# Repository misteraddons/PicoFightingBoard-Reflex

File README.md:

# Reflex Fighting Board

Open source PCB for arcade sticks using Raspberry Pi Pico's RP2040 microcontroller.

## Introduction

They say imitation is the highest form of flattery. If that's the case then the Brook line of arcade controller boards must be blushing beet red. The Reflex Fighting Board uses the same form factor and layout of the Brook PCBs to maintain compatibility with existing arcade stick cases, wiring harnesses, wire management accessories, etc.

The files for PCB production are in the [Releases](https://github.com/misteraddons/ReflexFightingBoard/tree/main/boards/Reflex_V1) section. The zip file contains the Gerber and drill files, which is all you'll need if you're soldering SMT components yourself. There are also `csv` files for the BOM (Bill of Materials) and component positioning for SMT assembly service.

I will also have premade boards periodically available for purchase at <https://misteraddons.com/collections/parts/products/reflex-encode-fighting-board>.

## Versions, Errata & Changelog

Reflex Encode V1.0:

>RGB LED voltage too low - voltage source moved to Vbus (before fuse) instead of +5V (after fuse)

>Pinout = PicoFightingBoard

Reflex Encode V1.1:

>Added USB A connector

>Added 5 pin USB header

>Pinout = GP2040

>Added turbo button

>Added turbo LED

>Added spinner header

>Error: Left and Right pins swapped compared to GP2040 pinout

>Error: TP+L3+R3 pinout incompatible with Brook cable

Reflex Encode V1.2:

>Fixed Left / Right pinout

>Fixed TP+L3+R3 pinout

## Firmware

The [GP2040](https://github.com/OpenStickCommunity/GP2040-CE) gamepad firmware for Pi Pico/RP2040 has a pre-configured build for use with the Reflex Fighting Board, providing support for XInput (PC, Android, Raspberry Pi, etc.), DInput (PC/PS3) and Nintendo Switch. [Go to the releases](https://github.com/OpenStickCommunity/GP2040-CE/releases) and download the `GP2040-CE_X.X.X_PicoFightingBoard.uf2`. To flash:

1. Unplug your Reflex Fighting Board.
1. Hold the BOOTSEL button on the Pico and plug into your computer. A new removable drive named `RPI-RP2` should appear in your file explorer.
1. Drag and drop the `GP2040-CE_X.X.X_PicoFightingBoard.uf2` file into the removable drive. This will flash the board.
1. The board should now be running the GP2040 firmware and should appear as a controller on your computer.

## Modification

If you want to modify the PCB layout you'll need the free [KiCad software](https://www.kicad.org/download/) installed. KiCad 6.x/7.x was used for these instructions.

## Support

If you would like to discuss and issues or features with the Reflex Fighting Board, please join the [OpenStick GP2040-CE Discord server](https://discord.gg/k2pxhke7q8) or the [MiSTer Addons Discord server](https://discord.gg/PtUFHtzuYD).

## Contributions

Want to help improve the Reflex Fighting Board? There are a bunch of ways to contribute!

### Pull Requests

Pull requests are welcome and encouraged for enhancements, fixes and documentation updates.

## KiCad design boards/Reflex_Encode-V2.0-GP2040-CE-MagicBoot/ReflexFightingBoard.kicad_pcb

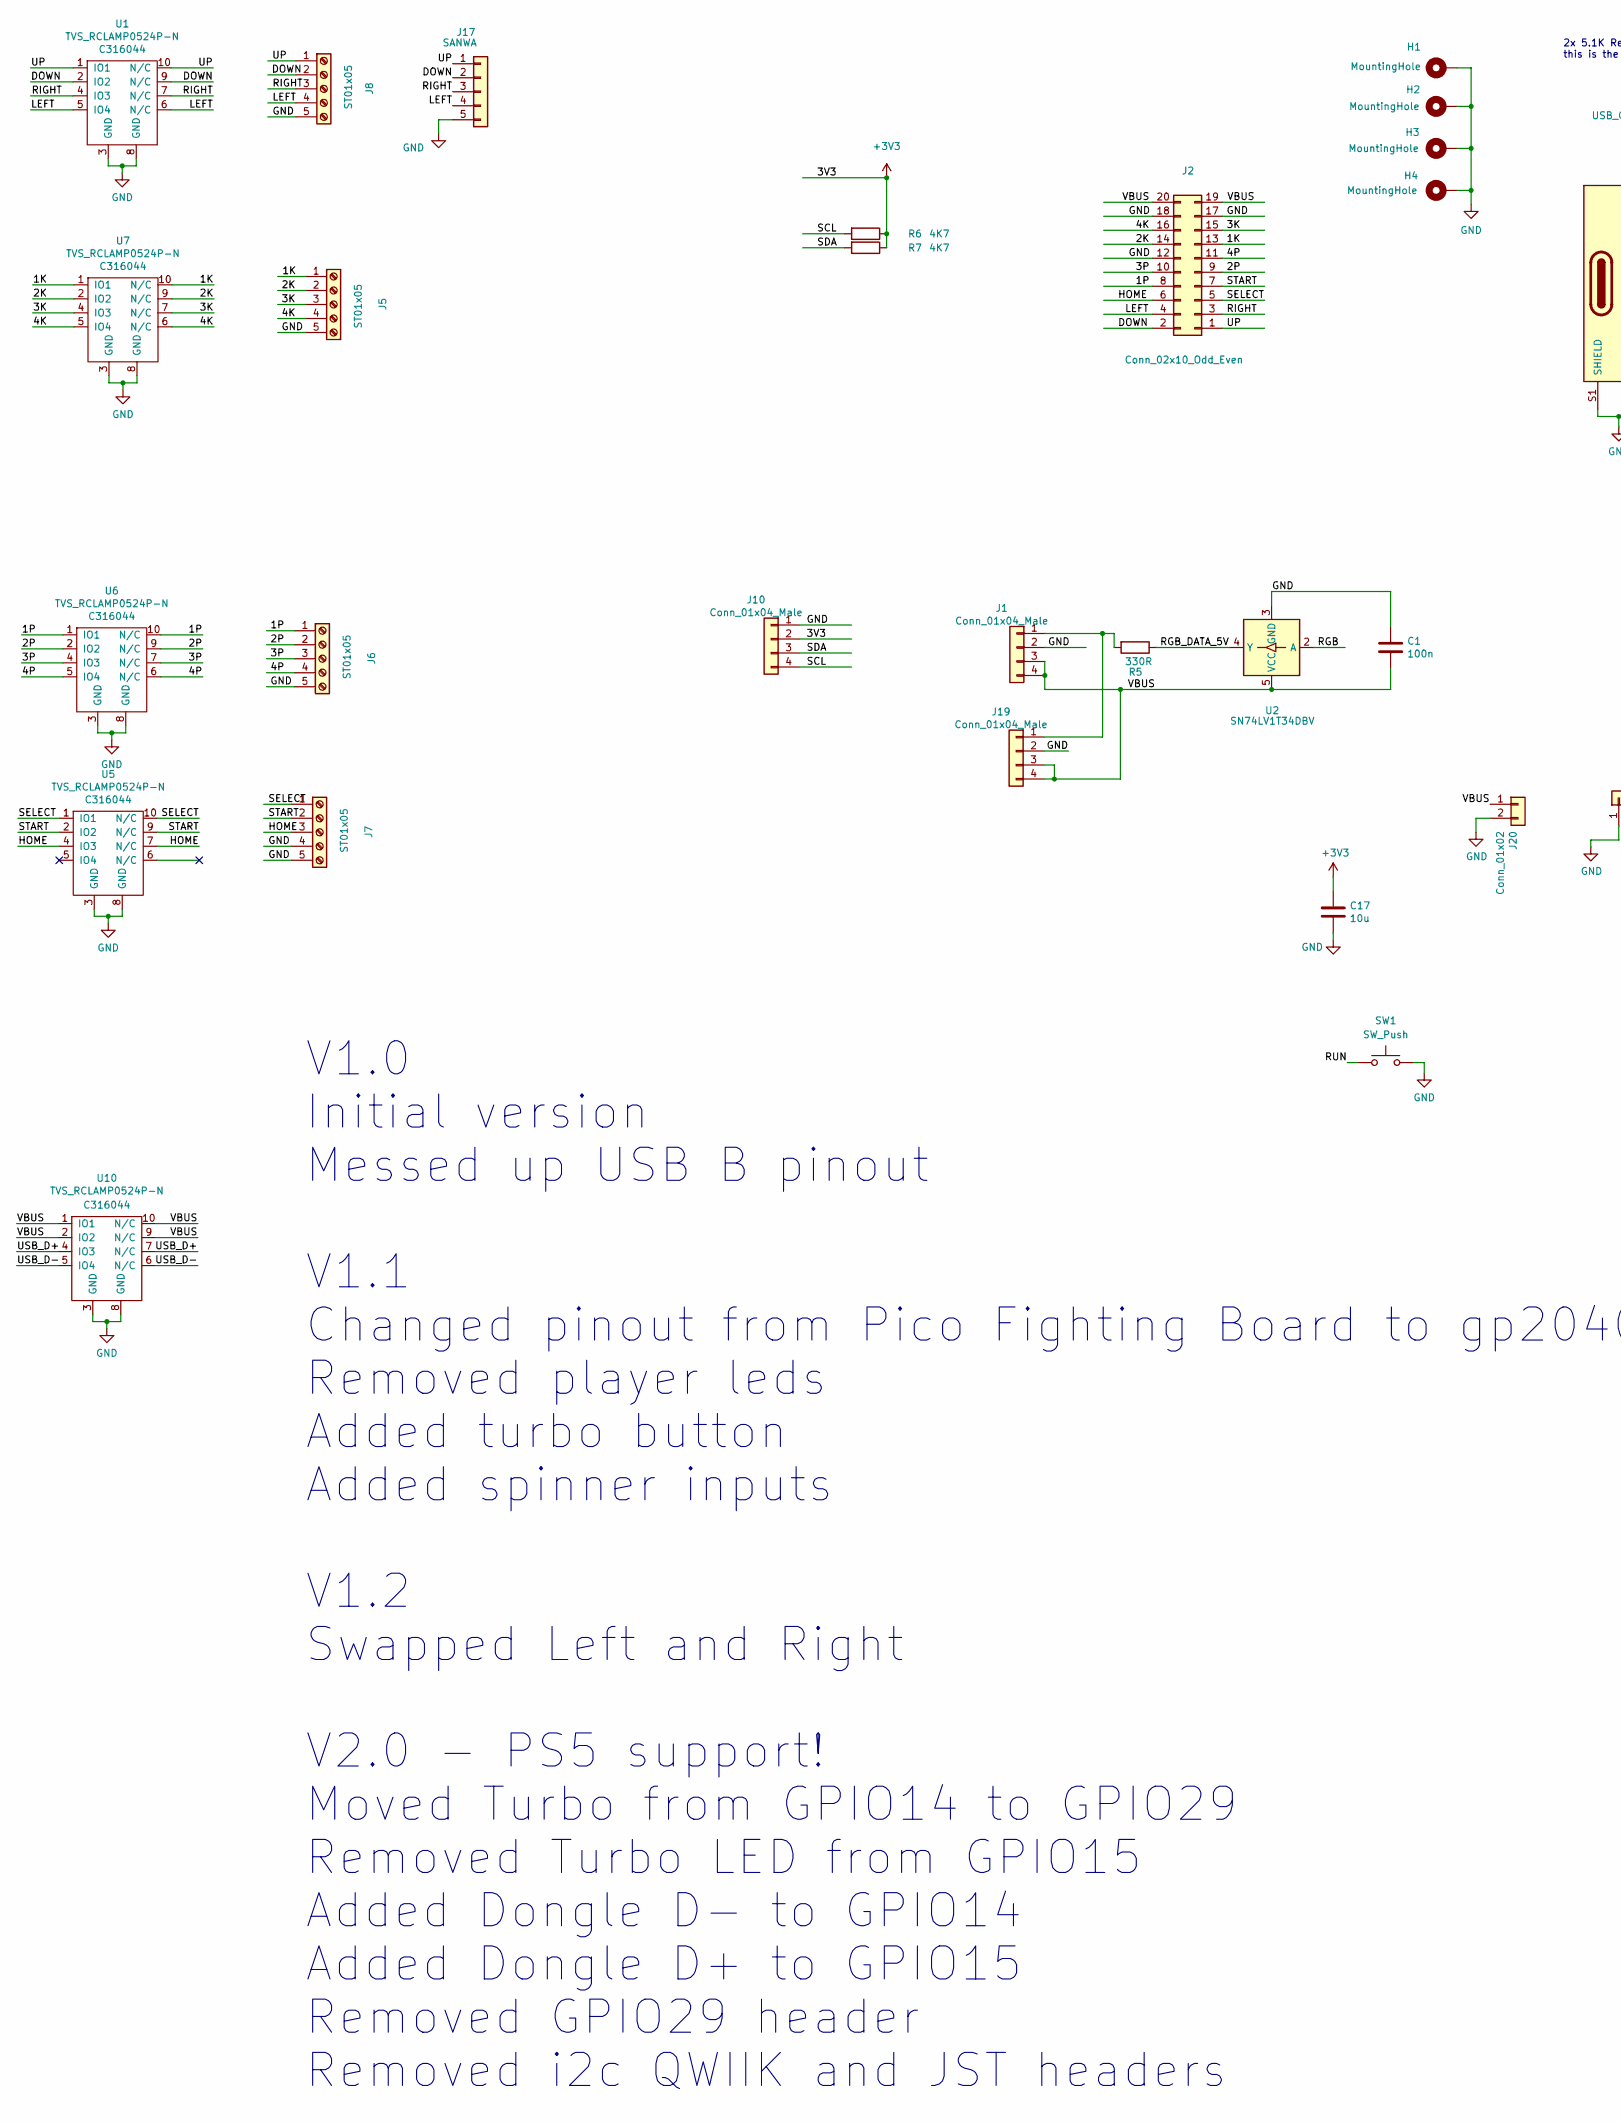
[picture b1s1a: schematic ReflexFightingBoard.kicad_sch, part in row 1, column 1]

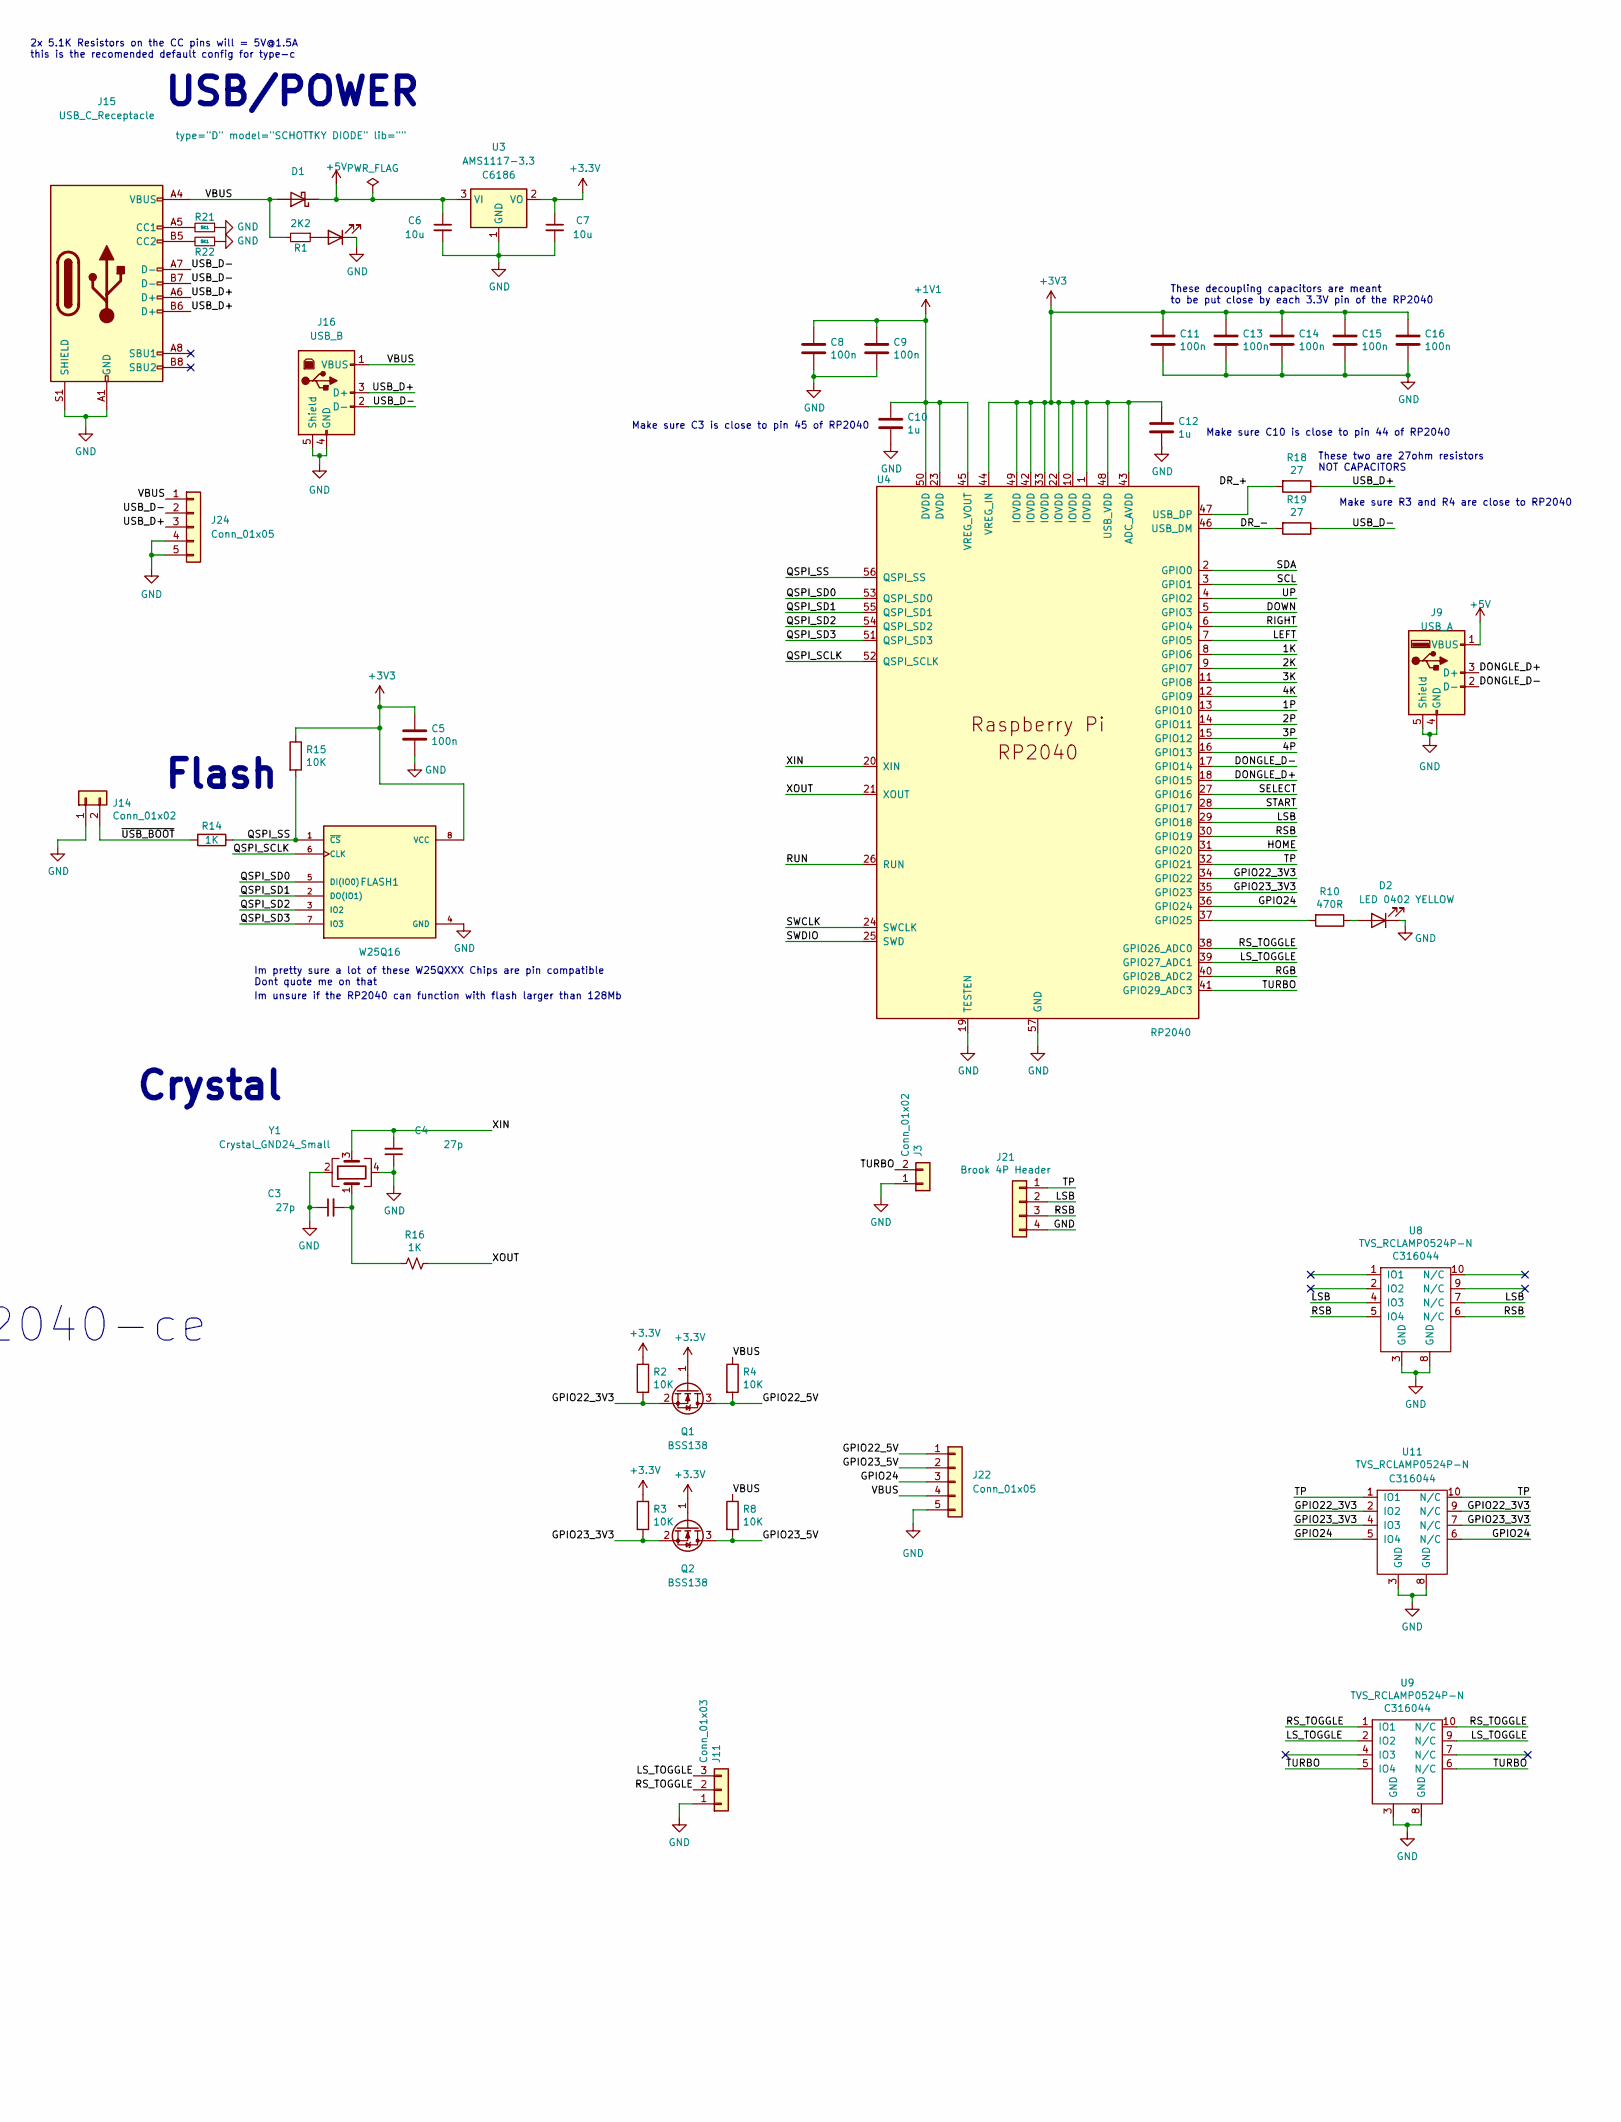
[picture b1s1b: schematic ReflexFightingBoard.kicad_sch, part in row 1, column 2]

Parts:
C1, C5, C8, C9, C11, C13, C14, C15, C16: 100n; C_0402_1005Metric; LCSC Part C1525
C3, C4: 27p; C_0402_1005Metric; LCSC Part C1557
C6, C7, C17: 10u; C_0402_1005Metric; LCSC Part C15525
C10, C12: 1u; C_0402_1005Metric; LCSC Part C52923
D1: type="D" model="SCHOTTKY DIODE" lib=""; D_0603_1608Metric; LCSC Part C143772
D2: LED; LED_0603_1608Metric; LCSC Part C5137313
FLASH1: W25Q16; SOIC127P790X216-8N; LCSC Part C82317
H1, H2, H3, H4: MountingHole; MountingHole_3.5mm_Pad
J1: Conn_01x04_Male; JST_PH_B4B-PH-K_1x04_P2.00mm_Vertical; LCSC Part C131334
J2: Conn_02x10_Odd_Even; PinHeader_2x10_P2.54mm_Vertical; LCSC Part C492427
J3: Conn_01x02; JST_PH_B2B-PH-K_1x02_P2.00mm_Vertical; LCSC Part C722767
J5, J6, J7, J8: ST01x05; TerminalBlock_MetzConnect_Type059_RT06305HBWC_1x05_P3.50mm_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; LCSC Part C3646874
J9: USB_A; USB2_A_HOR_C42425; LCSC Part C42425
J10, J19: Conn_01x04_Male; PinHeader_1x04_P2.54mm_Vertical; LCSC Part C2935910
J11: Conn_01x03; JST_PH_B3B-PH-K_1x03_P2.00mm_Vertical; LCSC Part C722771
J14, J20: Conn_01x02; PinHeader_1x02_P2.54mm_Vertical; LCSC Part C492401
J15: USB_C_Receptacle; USB_Type_C_C167321; LCSC Part C165948
J16: USB_B; USB_B_Lumberg_2411_02_Horizontal; LCSC Part C388656
J17: SANWA; JST_XH_B5B-XH-AM_1x05_P2.50mm_Vertical; LCSC Part C2908603
J21: Brook 4P Header; JST_PH_B4B-PH-K_1x04_P2.00mm_Vertical; LCSC Part C722775
J22, J24: Conn_01x05; PinHeader_1x05_P2.54mm_Vertical; LCSC Part C124379
Q1, Q2: BSS138; SOT-23; LCSC Part C8545
R1: 2K2; R_0402_1005Metric; LCSC Part C25879
R2, R3, R4, R8, R15: 10K; R_0402_1005Metric; LCSC Part C25744
R5: 330R; R_0402_1005Metric; LCSC Part C25104
R6, R7: 4K7; R_0402_1005Metric; LCSC Part C25900
R10: 470R; R_0402_1005Metric; LCSC Part C25117
R14: 1K; C_0402_1005Metric; LCSC Part C11702
R16: 1K; R_0402_1005Metric; LCSC Part C11702
R18, R19: 27; R_0402_1005Metric; LCSC Part C25100
R21, R22: 5K1; R_0402_1005Metric; LCSC Part C25905
SW1: SW_Push; SW_SPST_6x6_C499305_C499302; LCSC Part C499305
U1, U5, U6, U7, U8, U9, U10, U11: TVS_RCLAMP0524P-N; UDFN-10_1.35x2.6mm_P0.5mm; LCSC Part C316044
U2: SN74LV1T34DBV; SOT-23-5; LCSC Part C100024
U3: AMS1117-3.3; SOT-223-3_TabPin2; LCSC Part C6186
U4: RP2040; RP2040-QFN-56; LCSC Part C2040
Y1: Crystal_GND24_Small; Crystal_SMD_SeikoEpson_TSX3225-4Pin_3.2x2.5mm; LCSC Part C9002

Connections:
+1V1: C8.1, C9.1, C10.1, U4.23 (DVDD), U4.45 (VREG_VOUT), U4.50 (DVDD)
+5V: C6.1, D1.1 (K), J9.1 (VBUS), U3.3 (VI)
/1K: J2.13, J5.1, U4.8 (GPIO6), U7.1 (IO1), U7.10 (N/C)
/1P: J2.8, J6.1, U4.13 (GPIO10), U6.1 (IO1), U6.10 (N/C)
/2K: J2.14, J5.2, U4.9 (GPIO7), U7.2 (IO2), U7.9 (N/C)
/2P: J2.9, J6.2, U4.14 (GPIO11), U6.2 (IO2), U6.9 (N/C)
/3K: J2.15, J5.3, U4.11 (GPIO8), U7.4 (IO3), U7.7 (N/C)
/3P: J2.10, J6.3, U4.15 (GPIO12), U6.4 (IO3), U6.7 (N/C)
/4K: J2.16, J5.4, U4.12 (GPIO9), U7.5 (IO4), U7.6 (N/C)
/4P: J2.11, J6.4, U4.16 (GPIO13), U6.5 (IO4), U6.6 (N/C)
/DONGLE_D+: J9.3 (D+), U4.18 (GPIO15)
/DONGLE_D-: J9.2 (D-), U4.17 (GPIO14)
/DOWN: J2.2, J8.2, J17.2, U1.2 (IO2), U1.9 (N/C), U4.5 (GPIO3)
/DR_+: R18.2, U4.47 (USB_DP)
/DR_-: R19.2, U4.46 (USB_DM)
/GPIO22_3V3: Q1.2 (S), R2.2, U4.34 (GPIO22), U11.2 (IO2), U11.9 (N/C)
/GPIO22_5V: J22.1, Q1.3 (D), R4.2
/GPIO23_3V3: Q2.2 (S), R3.2, U4.35 (GPIO23), U11.4 (IO3), U11.7 (N/C)
/GPIO23_5V: J22.2, Q2.3 (D), R8.2
/GPIO24: J22.3, U4.36 (GPIO24), U11.5 (IO4), U11.6 (N/C)
/HOME: J2.6, J7.3, U4.31 (GPIO20), U5.4 (IO3), U5.7 (N/C)
/LEFT: J2.4, J8.4, J17.4, U1.5 (IO4), U1.6 (N/C), U4.7 (GPIO5)
/LSB: J21.2, U4.29 (GPIO18), U8.4 (IO3), U8.7 (N/C)
/LS_TOGGLE: J11.3, U4.39 (GPIO27_ADC1), U9.2 (IO2), U9.9 (N/C)
/QSPI_SCLK: FLASH1.6 (CLK), U4.52 (QSPI_SCLK)
/QSPI_SD0: FLASH1.5 (DI(IO0)), U4.53 (QSPI_SD0)
/QSPI_SD1: FLASH1.2 (DO(IO1)), U4.55 (QSPI_SD1)
/QSPI_SD2: FLASH1.3 (IO2), U4.54 (QSPI_SD2)
/QSPI_SD3: FLASH1.7 (IO3), U4.51 (QSPI_SD3)
/QSPI_SS: FLASH1.1 (~CS), R14.1, R15.2, U4.56 (QSPI_SS)
/RGB: U2.2 (A), U4.40 (GPIO28_ADC2)
/RGB_DATA_5V: R5.1, U2.4 (Y)
/RIGHT: J2.3, J8.3, J17.3, U1.4 (IO3), U1.7 (N/C), U4.6 (GPIO4)
/RSB: J21.3, U4.30 (GPIO19), U8.5 (IO4), U8.6 (N/C)
/RS_TOGGLE: J11.2, U4.38 (GPIO26_ADC0), U9.1 (IO1), U9.10 (N/C)
/RUN: SW1.1, U4.26 (RUN)
/SCL: J10.4, R6.2, U4.3 (GPIO1)
/SDA: J10.3, R7.2, U4.2 (GPIO0)
/SELECT: J2.5, J7.1, U4.27 (GPIO16), U5.1 (IO1), U5.10 (N/C)
/START: J2.7, J7.2, U4.28 (GPIO17), U5.2 (IO2), U5.9 (N/C)
/SWCLK: U4.24 (SWCLK)
/SWDIO: U4.25 (SWD)
/TP: J21.1, U4.32 (GPIO21), U11.1 (IO1), U11.10 (N/C)
/TURBO: J3.2, U4.41 (GPIO29_ADC3), U9.5 (IO4), U9.6 (N/C)
/UP: J2.1, J8.1, J17.1, U1.1 (IO1), U1.10 (N/C), U4.4 (GPIO2)
/USB_D+: J15.A6 (D+), J15.B6 (D+), J16.3 (D+), J24.3, R18.1, U10.4 (IO3), U10.7 (N/C)
/USB_D-: J15.A7 (D-), J15.B7 (D-), J16.2 (D-), J24.2, R19.1, U10.5 (IO4), U10.6 (N/C)
/VBUS: C1.2, D1.2 (A), J1.3, J1.4, J2.19, J2.20, J15.A4 (VBUS), J15.A9 (VBUS), J15.B4 (VBUS), J15.B9 (VBUS), J16.1 (VBUS), J19.3, J19.4, J20.1, J22.4, J24.1, R4.1, R8.1, U2.5 (VCC), U10.1 (IO1), U10.2 (IO2), U10.9 (N/C), U10.10 (N/C); also elsewhere on the board
/XIN: C4.2, U4.20 (XIN), Y1.3
/XOUT: R16.1, U4.21 (XOUT)
/~USB_BOOT: J14.2, R14.2
GND: C1.1, C3.1, C4.1, C5.2, C6.2, C7.2, C8.2, C9.2, C10.2, C11.2, C12.2, C13.2, C14.2, C15.2, C16.2, C17.2, D2.1 (K), FLASH1.4 (GND), H1.1, H2.1, H3.1, H4.1, J1.2, J2.12, J2.17, J2.18, J3.1, J5.5, J6.5, J7.4, J7.5, J8.5, J9.4 (GND), J9.5 (Shield), J10.1, J11.1, J14.1, J15.A1 (GND), J15.A12 (GND), J15.B1 (GND), J15.B12 (GND), J15.S1 (SHIELD), J16.4 (GND), J16.5 (Shield), J17.5, J19.2, J20.2, J21.4, J22.5, J24.4, J24.5, R21.1, R22.1, SW1.2, U1.3 (GND), U1.8 (GND), U2.3 (GND), U3.1 (GND), U4.19 (TESTEN), U4.57 (GND), U5.3 (GND), U5.8 (GND), U6.3 (GND), U6.8 (GND), U7.3 (GND), U7.8 (GND), U8.3 (GND), U8.8 (GND), U9.3 (GND), U9.8 (GND), U10.3 (GND), U10.8 (GND), U11.3 (GND), U11.8 (GND), Y1.2, Y1.4; also elsewhere on the board
unnamed: C3.2, R16.2, Y1.1
unnamed: J1.1, J19.1, R5.2
unnamed: J15.A5 (CC1), R21.2
unnamed: J15.B5 (CC2), R22.2
unnamed: R10.2, U4.37 (GPIO25)

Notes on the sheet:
Im pretty sure a lot of these W25QXXX Chips are pin compatible Dont quote me on that
Make sure C3 is close to pin 45 of RP2040
Make sure R3 and R4 are close to RP2040
These decoupling capacitors are meant to be put close by each 3.3V pin of the RP2040
These two are 27ohm resistors NOT CAPACITORS
Make sure C10 is close to pin 44 of RP2040
Flash
V1.0 Initial version Messed up USB B pinout V1.1 Changed pinout from Pico Fighting Board to gp2040-ce Removed player leds Added turbo button Added spinner inputs V1.2 Swapped Left and Right V2.0 - PS5 support! Moved Turbo from GPIO14 to GPIO29 Removed Turbo LED from GPIO15 Added Dongle D- to GPIO14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
2x 5.1K Resistors on the CC pins will = 5V@1.5A this is the recomended default config for type-c
Im unsure if the RP2040 can function with flash larger than 128Mb
USB/POWER
Crystal

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
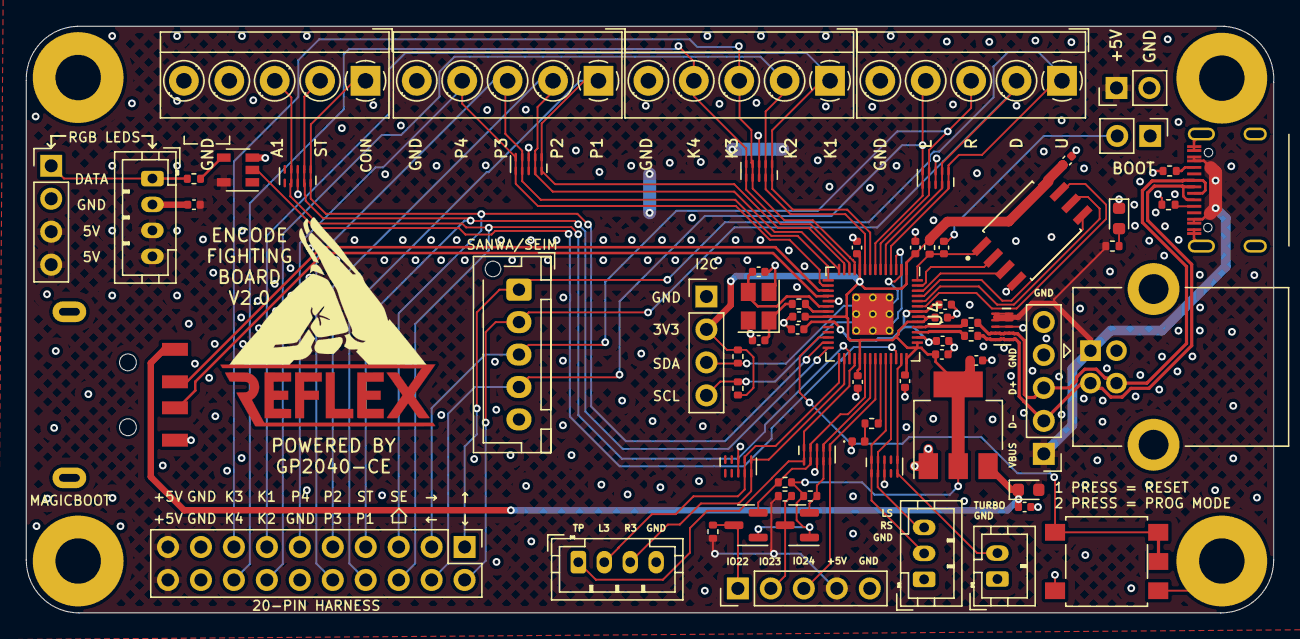
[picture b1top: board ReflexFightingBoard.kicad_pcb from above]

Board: 4 copper layers, 96.1 x 45.2 mm, 77 parts (1 on the bottom side), 58 nets.

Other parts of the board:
D3: LED; LED_0603_1608Metric
R9: 2K2; R_0402_1005Metric
Ref**: Val**; Reflex_Copper_20mm
Ref**#2: Val**; Reflex_Encode-Kung_Fu-Silk-15mm
Ref**#3: Val**; Idaho_M

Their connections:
/VBUS: R9.2; also elsewhere on the board
GND: D3.1 (K); also elsewhere on the board

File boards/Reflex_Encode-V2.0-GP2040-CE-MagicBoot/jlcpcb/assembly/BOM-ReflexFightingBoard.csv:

Comment,Designator,Footprint,LCSC
SN74LV1T34DBV,U2,SOT-23-5,C100024
1K,"R1,R14,R16",R_0402_1005Metric,C11702
Conn_01x05,"J22,J24",PinHeader_1x05_P2.54mm_Vertical,C124379
LED 0402 YELLOW,D2,LED_0402_1005Metric,C130719
Conn_01x04_Male,"J1,J12",JST_PH_B4B-PH-K_1x04_P2.00mm_Vertical,C131334
SCHOTTKY DIODE,D1,D_0603_1608Metric,C143772
Conn_01x04_Male,"J13,J9",BOOM_SH_C145961_1x04_P1.00mm_Vertical,C145961
100n,"C1,C11,C13,C14,C15,C16,C5,C8,C9",C_0402_1005Metric,C1525
10u,"C17,C6,C7",C_0402_1005Metric,C15525
27p,"C3,C4",C_0402_1005Metric,C1557
USB_C_Receptacle,J15,USB_Type_C_C167321,C165948
RP2040,U4,RP2040-QFN-56,C2040
27,"R18,R19",R_0402_1005Metric,C25100
330R,R5,R_0402_1005Metric,C25104
470R,R20,R_0402_1005Metric,C25117
10K,"R15,R2,R3,R4,R8",R_0402_1005Metric,C25744
4K7,"R6,R7",R_0402_1005Metric,C25900
5K1,"R21,R22",R_0402_1005Metric,C25905
SANWA,"J17,J18",JST_XH_B5B-XH-AM_1x05_P2.50mm_Vertical,C2908603
Conn_01x03,J11,JST_PH_B3B-PH-K_1x03_P2.00mm_Vertical,C2908624
Conn_01x04_Male,"J10,J19",PinHeader_1x04_P2.54mm_Vertical,C2935910
TVS_RCLAMP0524P-N,"U1,U10,U11,U5,U6,U7,U8,U9",UDFN-10_1.35x2.6mm_P0.5mm,C316044
ST01x05,"J5,J6,J7,J8",TerminalBlock_MetzConnect_Type059_RT06305HBWC_1x05_P3.50mm_Horizontal,C3646874
USB_B,J16,USB_B_Lumberg_2411_02_Horizontal,C388656
Conn_01x02,J20,PinHeader_1x02_P2.54mm_Vertical,C492401
Conn_02x10_Odd_Even,J2,PinHeader_2x10_P2.54mm_Vertical,C492427
SW_Push,SW1,SW_SPST_6x6_C499305_C499302,C499305
1u,"C10,C12",C_0402_1005Metric,C52923
AMS1117-3.3,U3,SOT-223-3_TabPin2,C6186
Conn_01x02,"J26,J3,J4",JST_PH_B2B-PH-K_1x02_P2.00mm_Vertical,C722767
Brook 4P Header,J21,JST_PH_B4B-PH-K_1x04_P2.00mm_Vertical,C722775
W25Q16,FLASH1,SOIC127P790X216-8N,C82317
BSS138,"Q1,Q2",SOT-23,C8545
Crystal_GND24_Small,Y1,Crystal_SMD_SeikoEpson_TSX3225-4Pin_3.2x2.5mm,C9002
Conn_01x02,J14,PinHeader_1x02_P2.54mm_Vertical,

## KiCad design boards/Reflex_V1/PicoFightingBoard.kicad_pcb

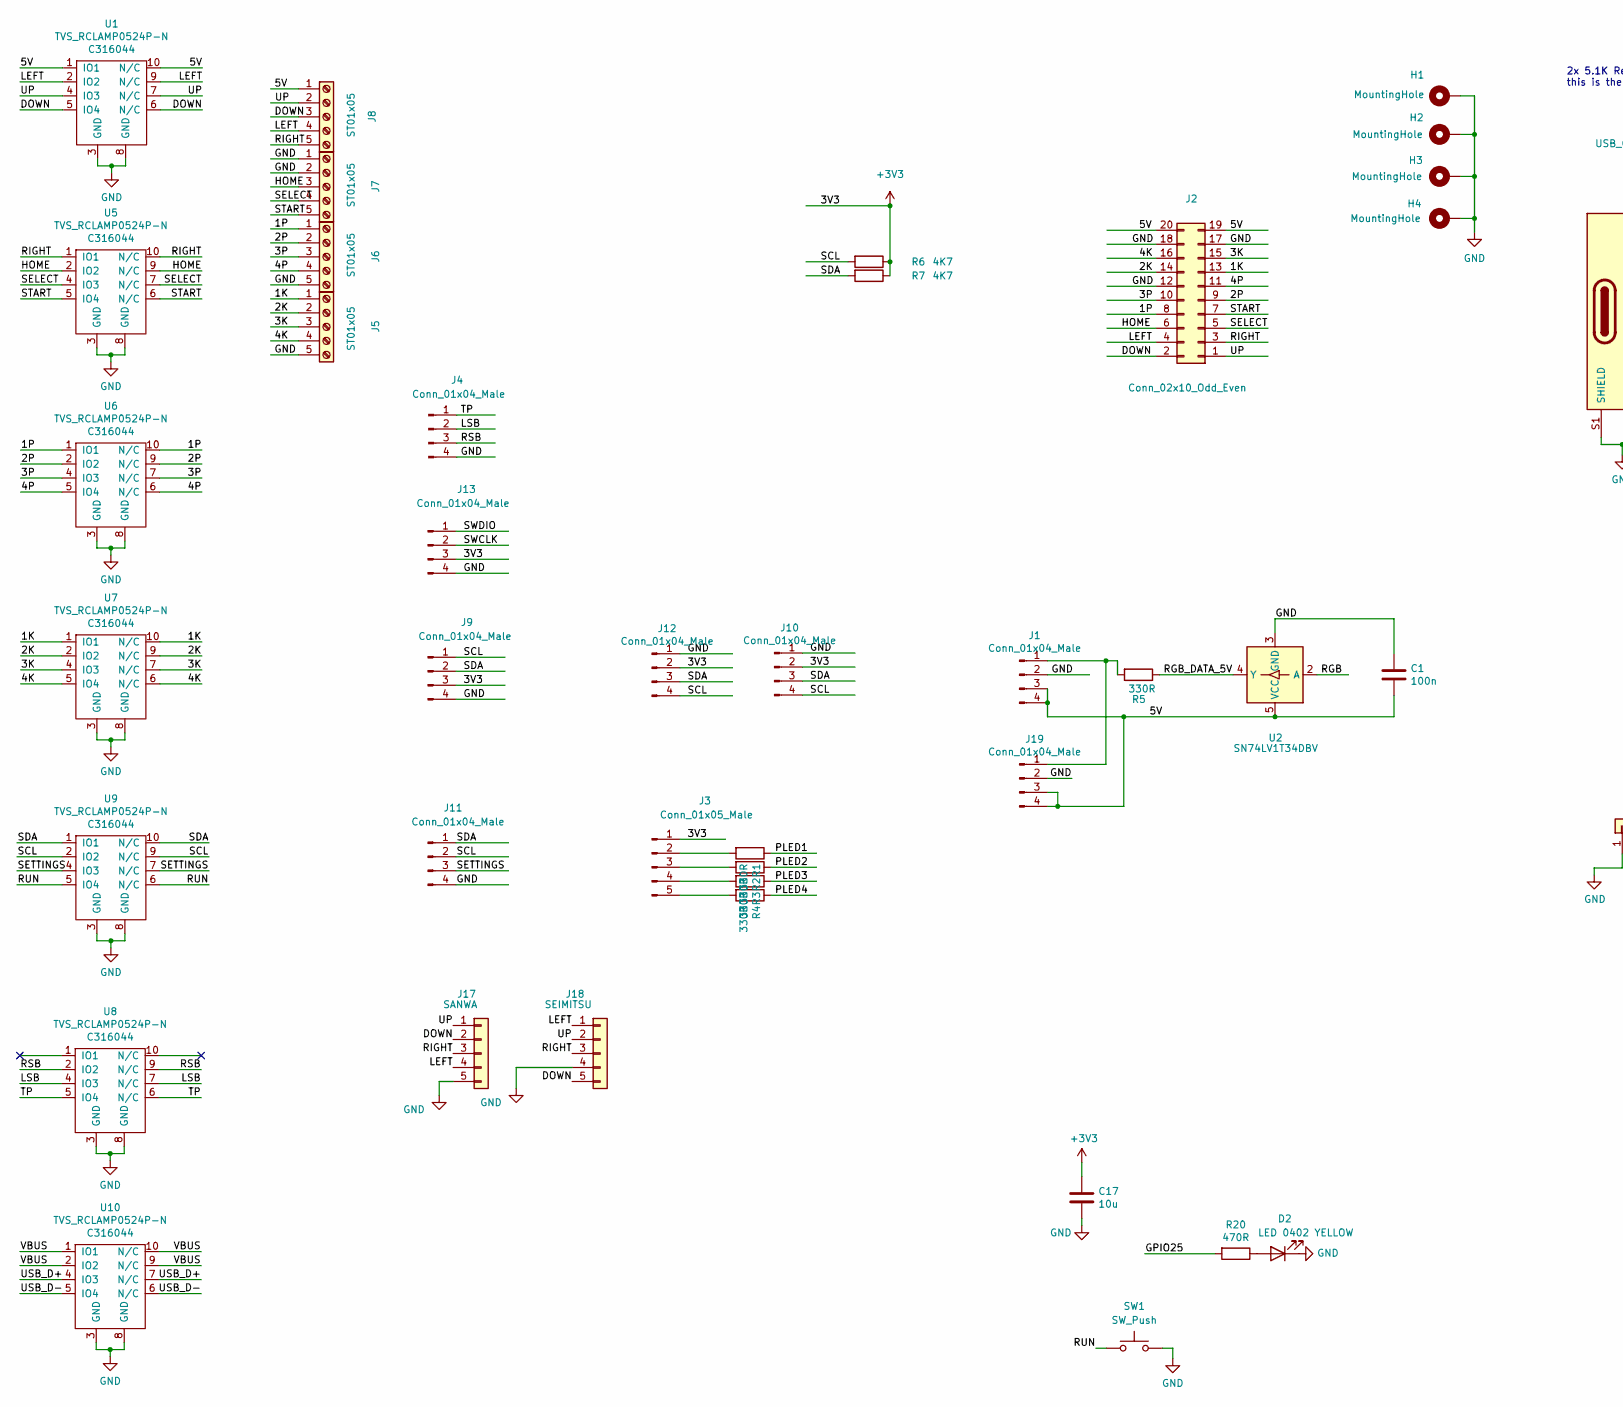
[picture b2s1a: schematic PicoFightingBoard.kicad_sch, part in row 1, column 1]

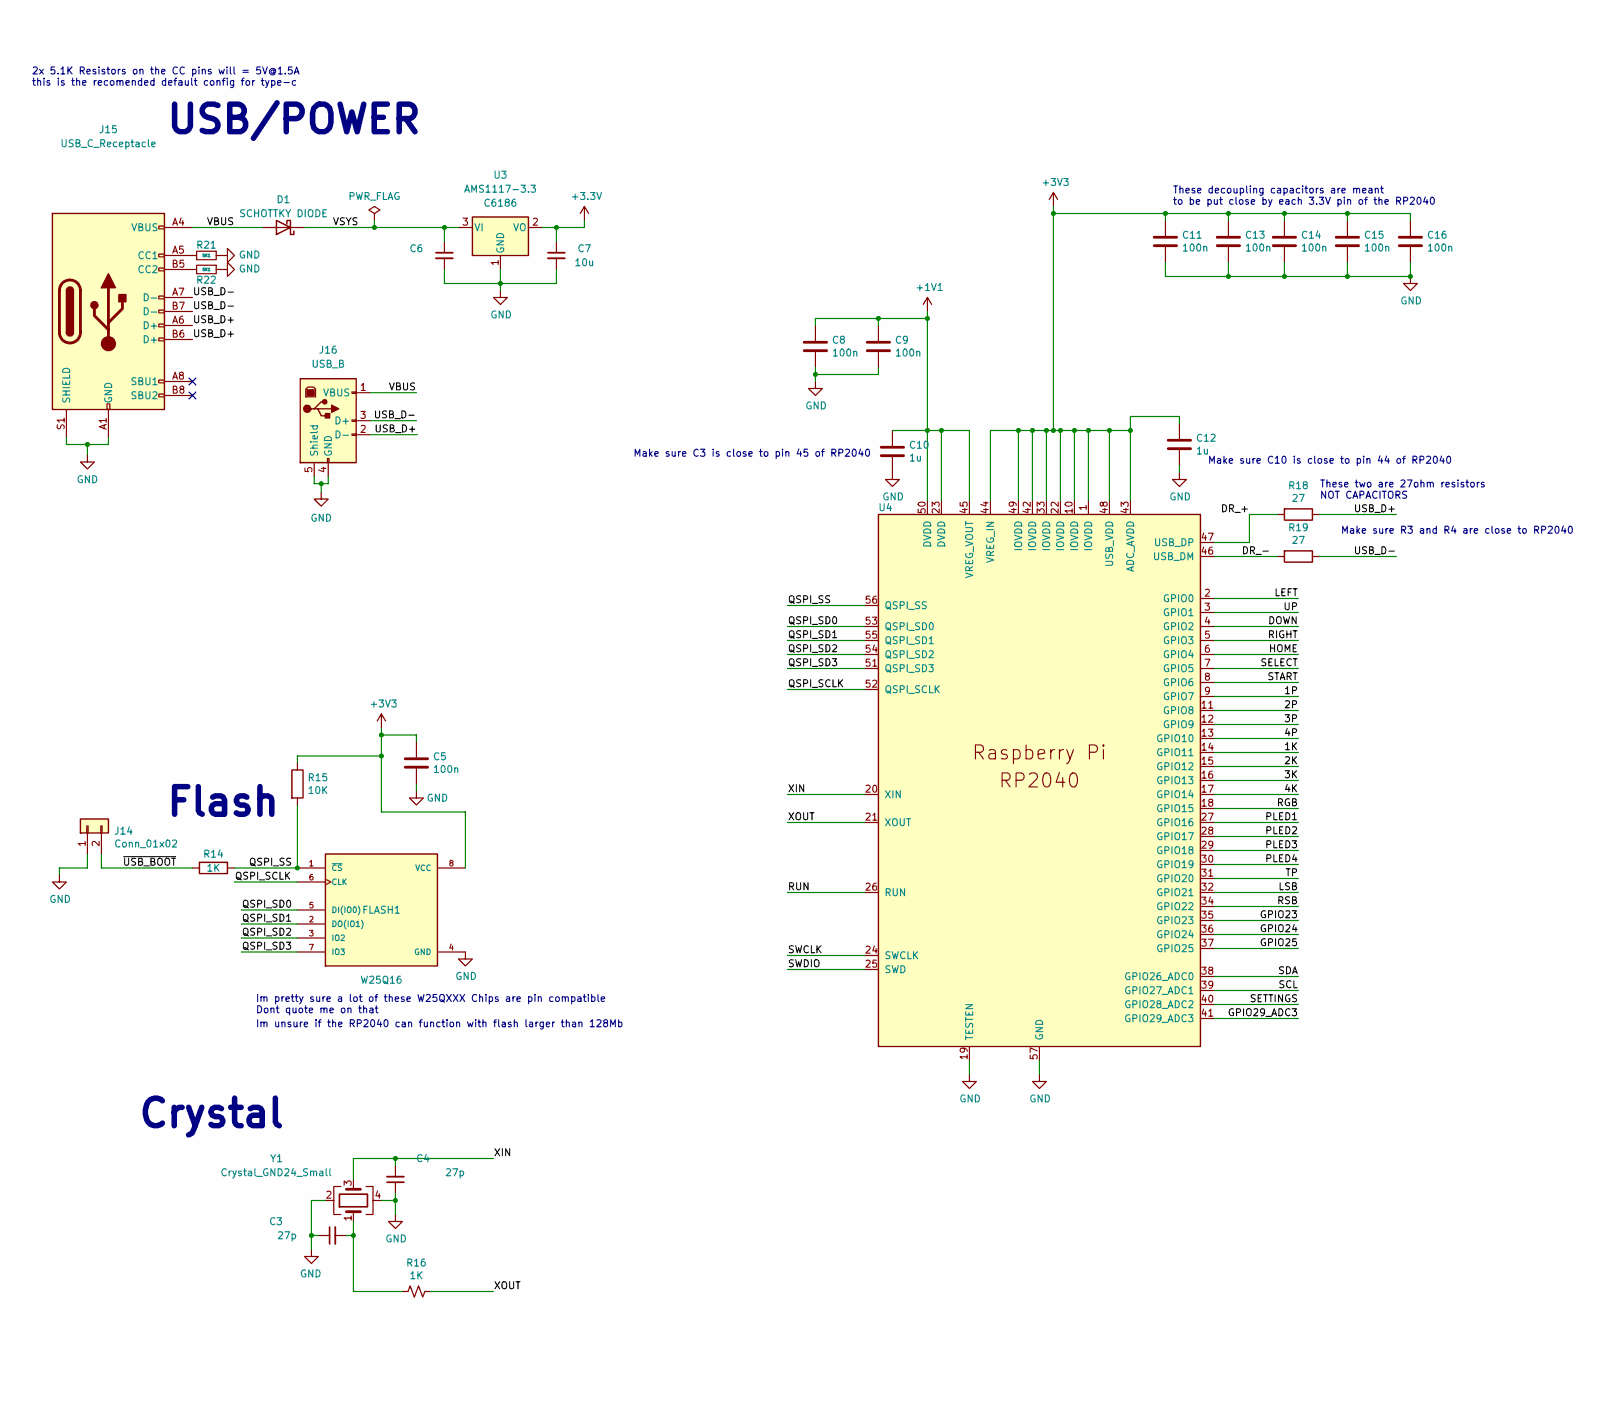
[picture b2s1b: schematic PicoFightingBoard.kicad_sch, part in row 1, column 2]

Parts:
C1, C5, C8, C9, C11, C13, C14, C15, C16: 100n; C_0402_1005Metric; LCSC Part C1525
C3, C4: 27p; C_0402_1005Metric; LCSC Part C1557
C6: LCSC Part C15525
C7, C17: 10u; C_0402_1005Metric; LCSC Part C15525
C10, C12: 1u; C_0402_1005Metric; LCSC Part C52923
D1: SCHOTTKY DIODE; D_0603_1608Metric; LCSC Part C143772
D2: LED 0402 YELLOW; LED_0402_1005Metric; LCSC Part C130719
FLASH1: W25Q16; SOIC127P790X216-8N; LCSC Part C82317
H1, H2, H3, H4: MountingHole; MountingHole_3.5mm_Pad
J1, J4, J11, J12: Conn_01x04_Male; JST_PH_B4B-PH-K_1x04_P2.00mm_Vertical; LCSC Part C131334
J2: Conn_02x10_Odd_Even; PinHeader_2x10_P2.54mm_Vertical; LCSC Part C492427
J3: Conn_01x05_Male; JST_PH_B5B-PH-K_1x05_P2.00mm_Vertical
J5, J6, J7, J8: ST01x05; TerminalBlock_MetzConnect_Type059_RT06305HBWC_1x05_P3.50mm_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; LCSC Part C3646874
J9, J13: Conn_01x04_Male; BOOM_SH_C145961_1x04_P1.00mm_Vertical; LCSC Part C145961
J10, J19: Conn_01x04_Male; PinHeader_1x04_P2.54mm_Vertical; LCSC Part C2935910
J14: Conn_01x02; PinHeader_1x02_P2.54mm_Vertical
J15: USB_C_Receptacle; USB_Type_C_C167321; LCSC Part C167321
J16: USB_B; USB_B_Lumberg_2411_02_Horizontal; LCSC Part C388656
J17: SANWA; JST_XH_B5B-XH-AM_1x05_P2.50mm_Vertical; LCSC Part C2908603
J18: SEIMITSU; JST_XH_B5B-XH-AM_1x05_P2.50mm_Vertical; LCSC Part C2908603
R1, R2, R3, R4, R5: 330R; R_0402_1005Metric; LCSC Part C25104
R6, R7: 4K7; R_0402_1005Metric; LCSC Part C25900
R14: 1K; C_0402_1005Metric; LCSC Part C11702
R15: 10K; R_0402_1005Metric; LCSC Part C25744
R16: 1K; R_0402_1005Metric; LCSC Part C11702
R18, R19: 27; R_0402_1005Metric; LCSC Part C25100
R20: 470R; R_0402_1005Metric; LCSC Part C25117
R21, R22: 5K1; R_0402_1005Metric; LCSC Part C25905
SW1: SW_Push; SW_SPST_6x6_C499305_C499302; LCSC Part C499305
U1, U5, U6, U7, U8, U9, U10: TVS_RCLAMP0524P-N; UDFN-10_1.35x2.6mm_P0.5mm; LCSC Part C316044
U2: SN74LV1T34DBV; SOT-23-5; LCSC Part C100024
U3: AMS1117-3.3; SOT-223-3_TabPin2; LCSC Part C6186
U4: LCSC Part C2040
Y1: Crystal_GND24_Small; Crystal_SMD_SeikoEpson_TSX3225-4Pin_3.2x2.5mm; LCSC Part C9002

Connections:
+1V1: C8.1, C9.1, C10.1, U4.23 (DVDD), U4.45 (VREG_VOUT), U4.50 (DVDD)
/1K: J2.13, J5.1, U4.14 (GPIO11), U7.1 (IO1), U7.10 (N/C)
/1P: J2.8, J6.1, U4.9 (GPIO7), U6.1 (IO1), U6.10 (N/C)
/2K: J2.14, J5.2, U4.15 (GPIO12), U7.2 (IO2), U7.9 (N/C)
/2P: J2.9, J6.2, U4.11 (GPIO8), U6.2 (IO2), U6.9 (N/C)
/3K: J2.15, J5.3, U4.16 (GPIO13), U7.4 (IO3), U7.7 (N/C)
/3P: J2.10, J6.3, U4.12 (GPIO9), U6.4 (IO3), U6.7 (N/C)
/4K: J2.16, J5.4, U4.17 (GPIO14), U7.5 (IO4), U7.6 (N/C)
/4P: J2.11, J6.4, U4.13 (GPIO10), U6.5 (IO4), U6.6 (N/C)
/5V: C1.2, J1.3, J1.4, J2.19, J2.20, J8.1, J19.3, J19.4, U1.1 (IO1), U1.10 (N/C), U2.5 (VCC)
/DOWN: J2.2, J8.3, J17.2, J18.5, U1.5 (IO4), U1.6 (N/C), U4.4 (GPIO2)
/DR_+: R18.2, U4.47 (USB_DP)
/DR_-: R19.2, U4.46 (USB_DM)
/GPIO23: U4.35 (GPIO23)
/GPIO24: U4.36 (GPIO24)
/GPIO25: R20.2, U4.37 (GPIO25)
/GPIO29_ADC3: U4.41 (GPIO29_ADC3)
/HOME: J2.6, J7.3, U4.6 (GPIO4), U5.2 (IO2), U5.9 (N/C)
/LEFT: J2.4, J8.4, J17.4, J18.1, U1.2 (IO2), U1.9 (N/C), U4.2 (GPIO0)
/LSB: J4.2, U4.32 (GPIO21), U8.4 (IO3), U8.7 (N/C)
/PLED1: R1.1, U4.27 (GPIO16)
/PLED2: R2.1, U4.28 (GPIO17)
/PLED3: R3.1, U4.29 (GPIO18)
/PLED4: R4.1, U4.30 (GPIO19)
/QSPI_SCLK: FLASH1.6 (CLK), U4.52 (QSPI_SCLK)
/QSPI_SD0: FLASH1.5 (DI(IO0)), U4.53 (QSPI_SD0)
/QSPI_SD1: FLASH1.2 (DO(IO1)), U4.55 (QSPI_SD1)
/QSPI_SD2: FLASH1.3 (IO2), U4.54 (QSPI_SD2)
/QSPI_SD3: FLASH1.7 (IO3), U4.51 (QSPI_SD3)
/QSPI_SS: FLASH1.1 (~CS), R14.1, R15.2, U4.56 (QSPI_SS)
/RGB: U2.2 (A), U4.18 (GPIO15)
/RGB_DATA_5V: R5.1, U2.4 (Y)
/RIGHT: J2.3, J8.5, J17.3, J18.3, U4.5 (GPIO3), U5.1 (IO1), U5.10 (N/C)
/RSB: J4.3, U4.34 (GPIO22), U8.2 (IO2), U8.9 (N/C)
/RUN: SW1.1, U4.26 (RUN), U9.5 (IO4), U9.6 (N/C)
/SCL: J9.1, J10.4, J11.2, J12.4, R6.2, U4.39 (GPIO27_ADC1), U9.2 (IO2), U9.9 (N/C)
/SDA: J9.2, J10.3, J11.1, J12.3, R7.2, U4.38 (GPIO26_ADC0), U9.1 (IO1), U9.10 (N/C)
/SELECT: J2.5, J7.4, U4.7 (GPIO5), U5.4 (IO3), U5.7 (N/C)
/SETTINGS: J11.3, U4.40 (GPIO28_ADC2), U9.4 (IO3), U9.7 (N/C)
/START: J2.7, J7.5, U4.8 (GPIO6), U5.5 (IO4), U5.6 (N/C)
/SWCLK: J13.2, U4.24 (SWCLK)
/SWDIO: J13.1, U4.25 (SWD)
/TP: J4.1, U4.31 (GPIO20), U8.5 (IO4), U8.6 (N/C)
/UP: J2.1, J8.2, J17.1, J18.2, U1.4 (IO3), U1.7 (N/C), U4.3 (GPIO1)
/USB_D+: J15.A6 (D+), J15.B6 (D+), J16.2 (D-), R18.1, U10.4 (IO3), U10.7 (N/C)
/USB_D-: J15.A7 (D-), J15.B7 (D-), J16.3 (D+), R19.1, U10.5 (IO4), U10.6 (N/C)
/VBUS: D1.2 (A), J15.A4 (VBUS), J15.A9 (VBUS), J15.B4 (VBUS), J15.B9 (VBUS), J16.1 (VBUS), U10.1 (IO1), U10.2 (IO2), U10.9 (N/C), U10.10 (N/C)
/VSYS: C6.1, D1.1 (K), U3.3 (VI)
/XIN: C4.2, U4.20 (XIN), Y1.3
/XOUT: R16.1, U4.21 (XOUT)
/~USB_BOOT: J14.2, R14.2
GND: C1.1, C3.1, C4.1, C5.2, C6.2, C7.2, C8.2, C9.2, C10.2, C11.2, C12.2, C13.2, C14.2, C15.2, C16.2, C17.2, D2.1 (K), FLASH1.4 (GND), H1.1, H2.1, H3.1, H4.1, J1.2, J2.12, J2.17, J2.18, J4.4, J5.5, J6.5, J7.1, J7.2, J9.4, J10.1, J11.4, J12.1, J13.4, J14.1, J15.A1 (GND), J15.A12 (GND), J15.B1 (GND), J15.B12 (GND), J15.S1 (SHIELD), J16.4 (GND), J16.5 (Shield), J17.5, J18.4, J19.2, R21.1, R22.1, SW1.2, U1.3 (GND), U1.8 (GND), U2.3 (GND), U3.1 (GND), U4.19 (TESTEN), U4.57 (GND), U5.3 (GND), U5.8 (GND), U6.3 (GND), U6.8 (GND), U7.3 (GND), U7.8 (GND), U8.3 (GND), U8.8 (GND), U9.3 (GND), U9.8 (GND), U10.3 (GND), U10.8 (GND), Y1.2, Y1.4
unnamed: C3.2, R16.2, Y1.1
unnamed: D2.2 (A), R20.1
unnamed: J1.1, J19.1, R5.2
unnamed: J3.2, R1.2
unnamed: J3.3, R2.2
unnamed: J3.4, R3.2
unnamed: J3.5, R4.2
unnamed: J15.A5 (CC1), R21.2
unnamed: J15.B5 (CC2), R22.2

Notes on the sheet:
Im pretty sure a lot of these W25QXXX Chips are pin compatible Dont quote me on that
Make sure C3 is close to pin 45 of RP2040
Make sure R3 and R4 are close to RP2040
These decoupling capacitors are meant to be put close by each 3.3V pin of the RP2040
These two are 27ohm resistors NOT CAPACITORS
Make sure C10 is close to pin 44 of RP2040
Flash
2x 5.1K Resistors on the CC pins will = 5V@1.5A this is the recomended default config for type-c
Im unsure if the RP2040 can function with flash larger than 128Mb
USB/POWER
Crystal

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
